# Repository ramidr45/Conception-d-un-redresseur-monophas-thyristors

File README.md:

# PFA — Conception d'un redresseur monophasé à thyristors

Projet de fin d'année (ENIT, génie électrique) : étude, simulation et conception d'un redresseur monophasé commandé à thyristors (BT152-800R) avec son circuit de commande (driver de gâchette).

## Contenu

| Dossier / fichier | Description |
|---|---|
| `Simulation_LTspice/` | Simulations LTspice : simple alternance, double alternance, pont complet (`SIM_finale/sim_PONT.asc`), train d'impulsions de commande |
| `kicad-redresseur/redresseur/` | Projet KiCad du redresseur : schéma, PCB, nomenclature (`.csv`), export PDF |
| `kicad-redresseur/librairie/Kicad/` | Symboles, empreintes et modèles 3D utilisés |
| `datasheets/` | Fiches techniques des composants (BT152, 2N2222, …) |
| `travail demandé/` | Cahier des charges et présentation |
| `PFA2_THYPON_FINALE.pdf`, `dim_Driver.pdf` | Rapport / dimensionnement du driver |

## Outils
- LTspice
- KiCad

## Notes
Les fichiers de résultats LTspice (`*.raw`) ne sont pas versionnés : relancer la simulation pour les régénérer.
Les librairies composants SamacSys / Ultra Librarian ne sont pas incluses (licence interdisant la redistribution) ; elles se téléchargent gratuitement sur componentsearchengine.com.

## Auteur
Rami Dridi — ENIT · [Portfolio](https://ramidr45.github.io) · [LinkedIn](https://www.linkedin.com/in/rami-dridi-103358327/)

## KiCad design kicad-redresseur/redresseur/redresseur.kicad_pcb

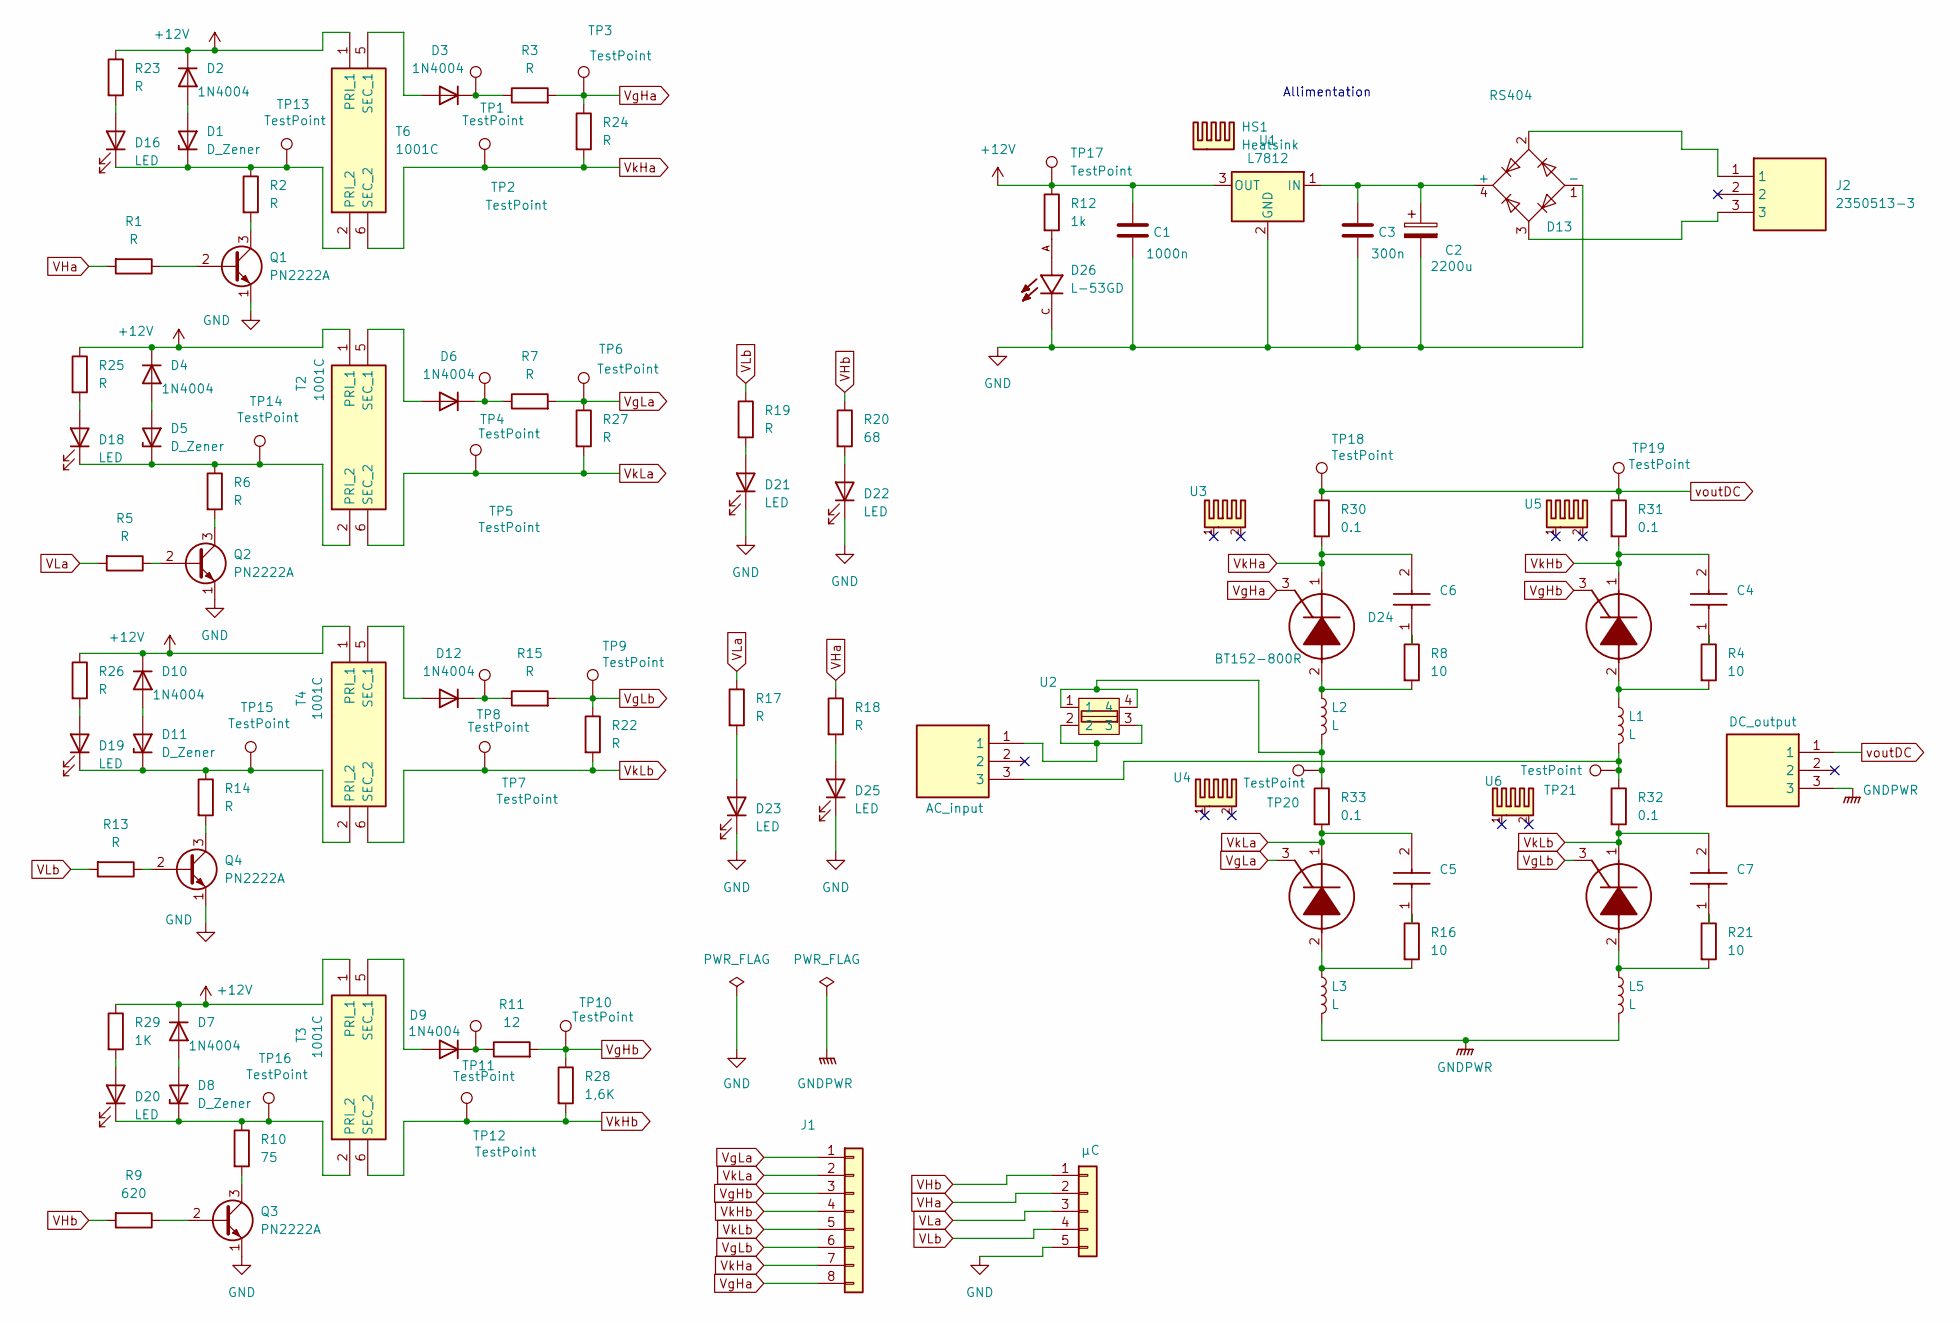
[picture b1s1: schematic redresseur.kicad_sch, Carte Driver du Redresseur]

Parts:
AC_input: 2350513-3; SHDRRA3W110P0X500_1X3_1660X1200X860P; Mouser Part Number 571-2350513-3
C1: 1000n; C_Rect_L7.0mm_W2.0mm_P5.00mm
C2: 2200u; CP_Radial_D18.0mm_P7.50mm
C3: 300n; C_Rect_L7.0mm_W2.0mm_P5.00mm
C4, C5, C6, C7: F471K33Y5RP6UK5R; Mouser Part Number 594-F471K33Y5RP6UK5R
D1, D5, D8, D11: D_Zener; D_DO-201_P12.70mm_Horizontal
D2, D3, D4, D6, D7, D9, D10, D12: 1N4004; D_DO-41_SOD81_P10.16mm_Horizontal
D13: RS404; RS-4L_DIO
D14, D15, D17, D24: BT152-800R; TO254P470X1000X2000-3P; Manufacturer_Part_Number BT152-800R
D16, D18, D19, D20, D21, D22, D23, D25: LED; LED_D3.0mm
D26: L-53GD; LEDRD254W50D500H1060; PARTREV V.3
DC_output: 2350513-3; SHDRRA3W110P0X500_1X3_1660X1200X860P; Mouser Part Number 571-2350513-3
HS1: Heatsink; Heatsink_Stonecold_HS-S01_13.21x6.35mm
J1: Conn_01x08; PinHeader_1x08_P2.54mm_Vertical
J2: 2350513-3; SHDRRA3W110P0X500_1X3_1660X1200X860P; Mouser Part Number 571-2350513-3
L1, L2, L3, L5: L; L_Axial_L13.0mm_D4.5mm_P15.24mm_Horizontal_Fastron_HCCC
Q1, Q2, Q3, Q4: PN2222A; TO-92_Inline
R1, R2, R3, R5, R6, R7, R13, R14, R15, R17, R18, R19, R22, R23, R24, R25, R26, R27: R; R_Axial_DIN0207_L6.3mm_D2.5mm_P10.16mm_Horizontal
R4, R8, R16, R21: 10; R_Axial_DIN0207_L6.3mm_D2.5mm_P10.16mm_Horizontal
R9: 620; R_Axial_DIN0207_L6.3mm_D2.5mm_P10.16mm_Horizontal
R10: 75; R_Axial_DIN0207_L6.3mm_D2.5mm_P10.16mm_Horizontal
R11: 12; R_Axial_DIN0207_L6.3mm_D2.5mm_P10.16mm_Horizontal
R12: 1k; R_Axial_DIN0207_L6.3mm_D2.5mm_P10.16mm_Horizontal
R20: 68; R_Axial_DIN0207_L6.3mm_D2.5mm_P10.16mm_Horizontal
R28: 1,6K; R_Axial_DIN0207_L6.3mm_D2.5mm_P10.16mm_Horizontal
R29: 1K; R_Axial_DIN0207_L6.3mm_D2.5mm_P10.16mm_Horizontal
R30, R31, R32, R33: 0.1; R_Axial_Power_L20.0mm_W6.4mm_P22.40mm
T2, T3, T4, T6: 1001C; Mouser Part Number 580-1001C
TP1, TP2, TP3, TP4, TP5, TP6, TP7, TP8, TP9, TP10, TP11, TP12, TP13, TP14, TP15, TP16, TP17, TP18, TP19, TP20, TP21: TestPoint; TestPoint_Loop_D1.80mm_Drill1.0mm_Beaded
U1: L7812; TO-220-3_Vertical
U2: 3101.0045.15; 3101004515; Manufacturer_Part_Number 3101.0045.15; Mouser Part Number 693-3101.0045.15
U3, U4, U5, U6: RA-T2X-51E; RAT2X51E; Manufacturer_Part_Number RA-T2X-51E; Mouser Part Number 588-RA-T2X-51E
µC: Conn_01x05; PinHeader_1x05_P2.54mm_Vertical

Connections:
+12V: C1.1, D2.1 (K), D4.1 (K), D7.1 (K), D10.1 (K), R12.1, R23.1, R25.1, R26.1, R29.1, T2.1 (PRI_1), T3.1 (PRI_1), T4.1 (PRI_1), T6.1 (PRI_1), TP17.1, U1.3 (OUT)
GND: C1.2, C2.2, C3.2, D13.1 (-), D21.1 (K), D22.1 (K), D23.1 (K), D25.1 (K), D26.C, Q1.1 (E), Q2.1 (E), Q3.1 (E), Q4.1 (E), U1.2 (GND), µC.5; also elsewhere on the board
GNDPWR: DC_output.3, L3.2, L5.2; also elsewhere on the board
unnamed 3: AC_input.1, U2.2, U2.3; also elsewhere on the board
unnamed 4: AC_input.3, L1.2, R32.1, TP21.1; also elsewhere on the board
unnamed: C4.1, R4.1
unnamed: C5.1, R16.1
unnamed: C6.1, R8.1
unnamed: C7.1, R21.1
unnamed: D1.2 (A), D2.2 (A)
unnamed: D1.1 (K), D16.1 (K), R2.1, T6.2 (PRI_2), TP13.1
unnamed: D3.2 (A), T6.5 (SEC_1)
unnamed: D3.1 (K), R3.1, TP1.1
unnamed: D4.2 (A), D5.2 (A)
unnamed: D6.2 (A), T2.5 (SEC_1)
unnamed: D6.1 (K), R7.1, TP4.1
unnamed: D7.2 (A), D8.2 (A)
unnamed: D9.2 (A), T3.5 (SEC_1)
unnamed: D9.1 (K), R11.1, TP11.1
unnamed: D10.2 (A), D11.2 (A)
unnamed: D11.1 (K), D19.1 (K), R14.1, T4.2 (PRI_2), TP15.1
unnamed: D12.2 (A), T4.5 (SEC_1)
unnamed: D12.1 (K), R15.1, TP8.1
unnamed: C2.1, C3.1, D13.4 (+), U1.1 (IN)
unnamed: D13.2, J2.1
unnamed: D13.3, J2.3
unnamed: D14.2 (A), L3.1, R16.2
unnamed: D15.2 (A), L1.1, R4.2
unnamed: D16.2 (A), R23.2
unnamed: D17.2 (A), L5.1, R21.2
unnamed: D18.2 (A), R25.2
unnamed: D5.1 (K), D18.1 (K), R6.1, T2.2 (PRI_2), TP14.1
unnamed: D19.2 (A), R26.2
unnamed: D20.2 (A), R29.2
unnamed: D8.1 (K), D20.1 (K), R10.1, T3.2 (PRI_2), TP16.1
unnamed: D21.2 (A), R19.2
unnamed: D22.2 (A), R20.2
unnamed: D23.2 (A), R17.2
unnamed: D24.2 (A), L2.1, R8.2
unnamed: D25.2 (A), R18.2
unnamed: D26.A, R12.2
unnamed: L2.2, R33.1, TP20.1, U2.1, U2.4
unnamed: Q1.2 (B), R1.1
unnamed: Q1.3 (C), R2.2
unnamed: Q2.2 (B), R5.1
unnamed: Q2.3 (C), R6.2
unnamed: Q3.2 (B), R9.1
unnamed: Q3.3 (C), R10.2
unnamed: Q4.2 (B), R13.1
unnamed: Q4.3 (C), R14.2
VHa: R1.2, R18.1, µC.2; also elsewhere on the board
VHb: R9.2, R20.1, µC.1; also elsewhere on the board
VLa: R5.2, R17.1, µC.3; also elsewhere on the board
VLb: R13.2, R19.1, µC.4; also elsewhere on the board
VgHa: D24.3 (G), J1.8, R3.2, R24.1, TP3.1
VgHb: D15.3 (G), J1.3, R11.2, R28.1, TP10.1
VgLa: D14.3 (G), J1.1, R7.2, R27.1, TP6.1
VgLb: D17.3 (G), J1.6, R15.2, R22.1, TP9.1
VkHa: C6.2, D24.1 (K), J1.7, R24.2, R30.2, T6.6 (SEC_2), TP2.1
VkHb: C4.2, D15.1 (K), J1.4, R28.2, R31.2, T3.6 (SEC_2), TP12.1
VkLa: C5.2, D14.1 (K), J1.2, R27.2, R33.2, T2.6 (SEC_2), TP5.1
VkLb: C7.2, D17.1 (K), J1.5, R22.2, R32.2, T4.6 (SEC_2), TP7.1
voutDC: DC_output.1, R30.1, R31.1, TP18.1, TP19.1; also elsewhere on the board

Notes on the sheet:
Allimentation

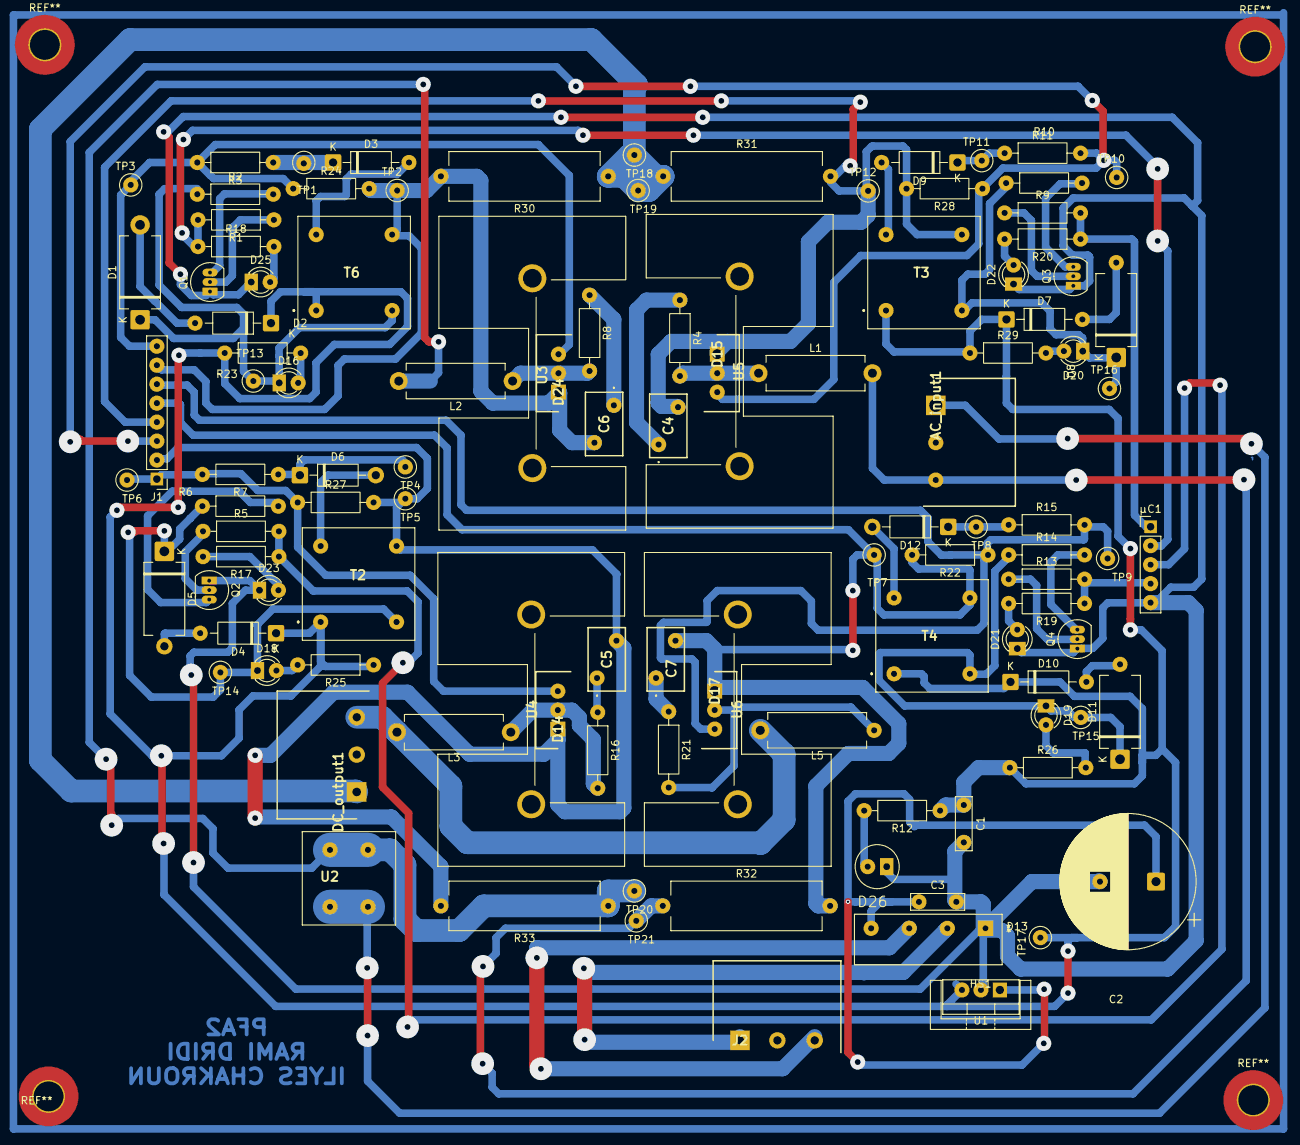
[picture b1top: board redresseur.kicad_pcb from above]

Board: 4 copper layers, 111 parts (0 on the bottom side), 63 nets.

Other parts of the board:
AC_input1: 2350513-3; SHDRRA3W110P0X500_1X3_1660X1200X860P
DC_output1: 2350513-3; SHDRRA3W110P0X500_1X3_1660X1200X860P
µC1: Conn_01x05; PinHeader_1x05_P2.54mm_Vertical

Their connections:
GND: µC1.5; also elsewhere on the board
GNDPWR: DC_output1.3; also elsewhere on the board
unnamed 3: AC_input1.1; also elsewhere on the board
unnamed 4: AC_input1.3; also elsewhere on the board
VHa: µC1.2; also elsewhere on the board
VHb: µC1.1; also elsewhere on the board
VLa: µC1.3; also elsewhere on the board
VLb: µC1.4; also elsewhere on the board
voutDC: DC_output1.1; also elsewhere on the board
